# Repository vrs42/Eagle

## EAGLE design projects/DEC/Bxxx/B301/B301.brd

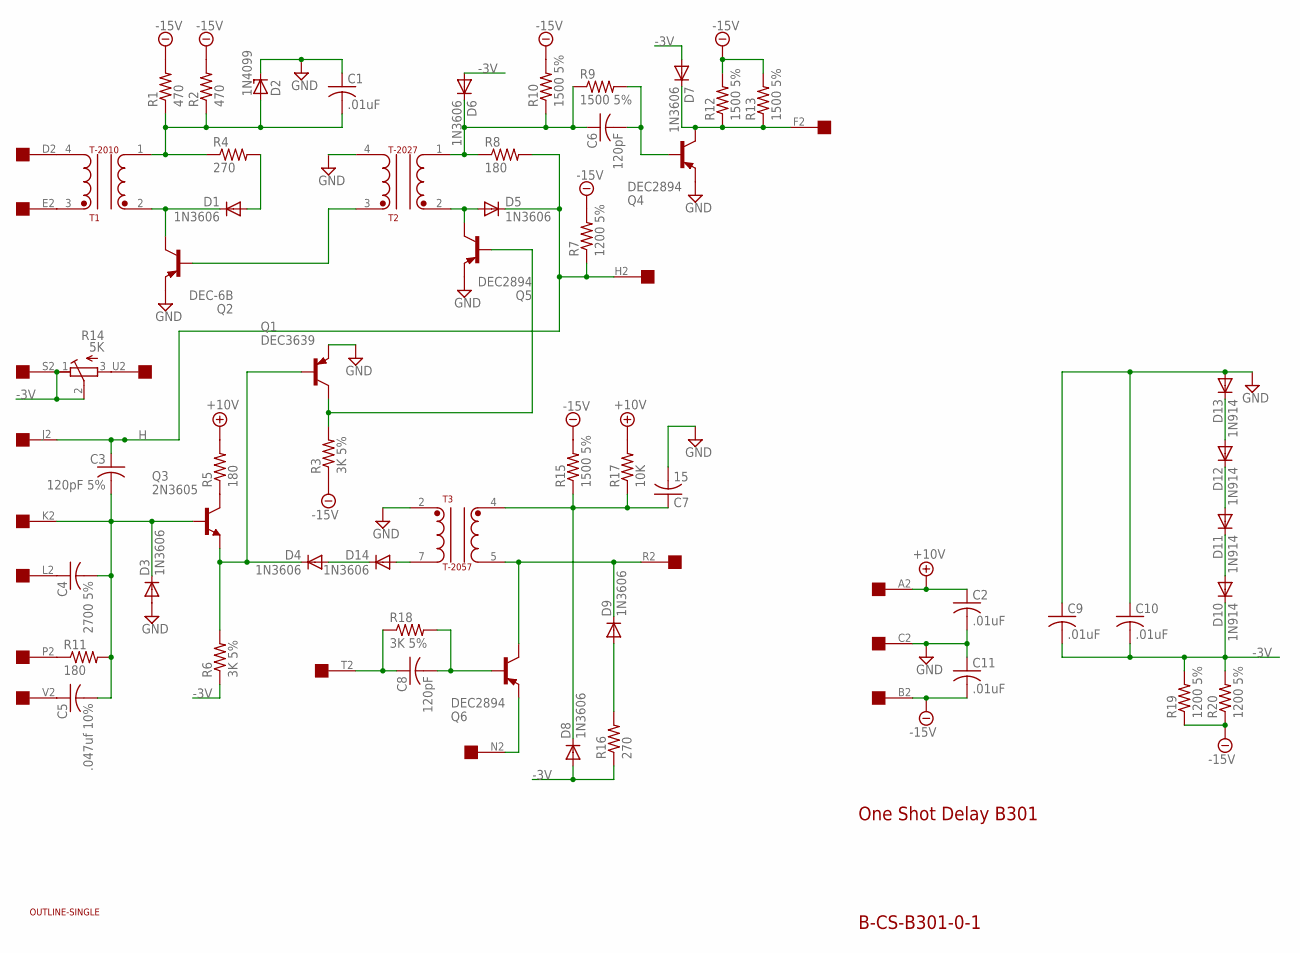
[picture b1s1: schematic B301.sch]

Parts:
C1, C2, C9, C10, C11: .01uF; C050-025X075
C3: 120pF 5%; C050-025X075
C4: 2700 5%; C102-043X133
C5: .047uf 10%; C225-062X268
C6, C8: 120pF; C050-025X075
C7: 15; C050-025X075
D1, D3, D4, D5, D6, D7, D8, D9, D14: 1N3606; DO35-10
D2: 1N4099; DO35Z10
D10, D11, D12, D13: 1N914; DO35-10
Q1: DEC3639; TO39
Q2: DEC-6B; TO39
Q3: 2N3605; TO39
Q4, Q5, Q6: DEC2894; TO39
R1, R2: 470; 0207/10
R3, R6, R18: 3K 5%; 0207/10
R4, R16: 270; 0207/10
R5, R8, R11: 180; 0207/10
R7, R19, R20: 1200 5%; 0207/10
R9, R10, R12, R13, R15: 1500 5%; 0207/10
R14: 5K; 3006Y
R17: 10K; 0207/10
T1: T-2010; TRANSFORMER2
T2: T-2027; TRANSFORMER2
T3: T-2057; TRANSFORMER
U$1: OUTLINE-SINGLE; SINGLE
U$2: EDGE-1; EDGE-CON1

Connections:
+10V: C2.1, R5.2, R17.2, U$2.A2
-3V: C9.2, C10.2, D6.A, D7.A, D8.A, D10.C, R6.1, R14.1 (A), R14.2 (S), R16.1, R19.2, R20.2, U$2.S2
-15V: C11.2, R1.2, R2.2, R3.1, R7.2, R10.2, R12.2, R13.2, R15.2, R19.1, R20.1, U$2.B2
GND: C1.1, C2.2, C7.2, C9.1, C10.1, C11.1, D2.C, D3.A, D13.A, Q1.1 (E), Q2.1 (E), Q4.1 (E), Q5.1 (E), T2.4, T3.2, U$2.C2
H: C3.1, D5.C, R7.1, R8.2, U$2.H2, U$2.J2
unnamed: D7.C, Q4.3 (C), R12.1, R13.1, U$2.F2
unnamed: C6.2, Q4.2 (B), R9.2
unnamed: D4.A, D14.C
unnamed: C3.2, C4.2, C5.2, D3.C, Q3.2 (B), R11.2, U$2.K2
unnamed: R14.3 (E), U$2.U2
unnamed: C4.1, U$2.L2
unnamed: C5.1, U$2.V2
unnamed: Q2.2 (B), T2.3
unnamed: D1.C, Q2.3 (C), T1.2
unnamed: R11.1, U$2.P2
unnamed: Q3.3 (C), R5.1
unnamed: C1.2, D2.A, R1.1, R2.1, R4.1, T1.1
unnamed: D1.A, R4.2
unnamed: D5.A, Q5.3 (C), T2.2
unnamed: D4.C, Q1.2 (B), Q3.1 (E), R6.2
unnamed: C6.1, D6.C, R8.1, R9.1, R10.1, T2.1
unnamed: Q1.3 (C), Q5.2 (B), R3.2
unnamed: D14.A, T3.7
unnamed: D9.C, Q6.3 (C), T3.5, U$2.R2
unnamed: Q6.1 (E), U$2.N2
unnamed: C8.2, Q6.2 (B), R18.2
unnamed: C8.1, R18.1, U$2.T2
unnamed: C7.1, D8.C, R15.1, R17.1, T3.4
unnamed: D9.A, R16.2
unnamed: D12.A, D13.C
unnamed: D11.A, D12.C
unnamed: D10.A, D11.C
unnamed: T1.3, U$2.E2
unnamed: T1.4, U$2.D2

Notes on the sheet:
One Shot Delay B301
B-CS-B301-0-1

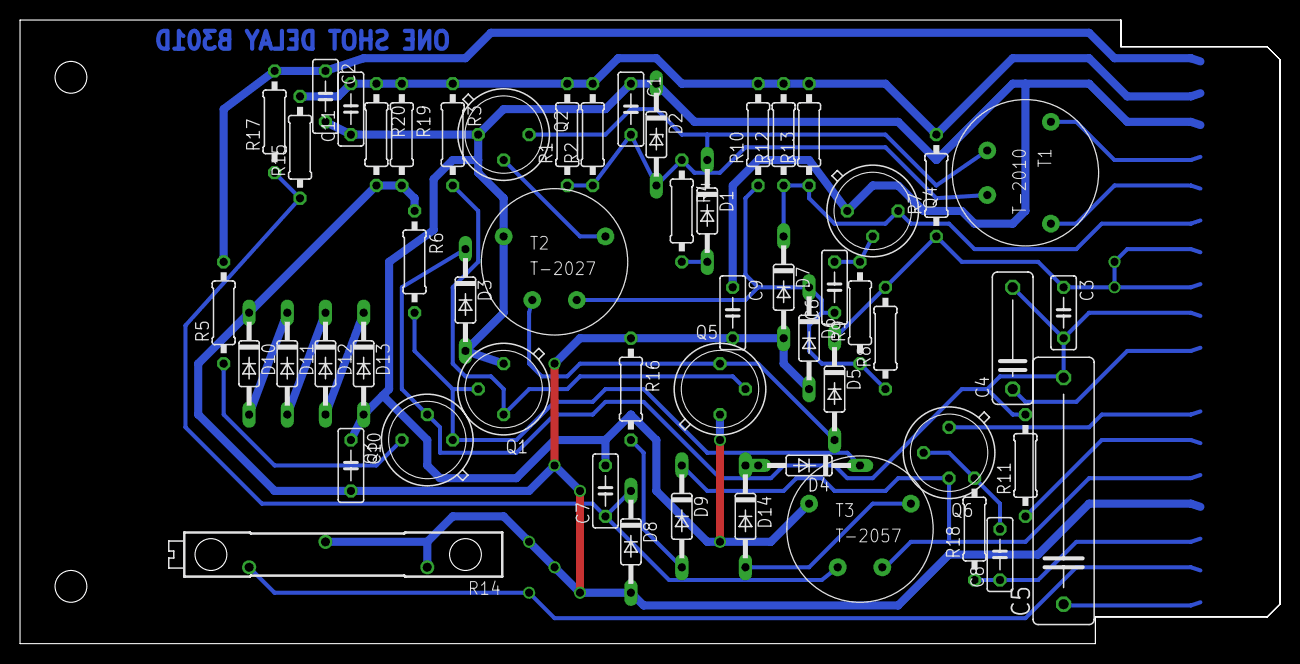
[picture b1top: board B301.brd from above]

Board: 2 copper layers, 125.7 x 62.2 mm, 56 parts (0 on the bottom side), 34 nets.

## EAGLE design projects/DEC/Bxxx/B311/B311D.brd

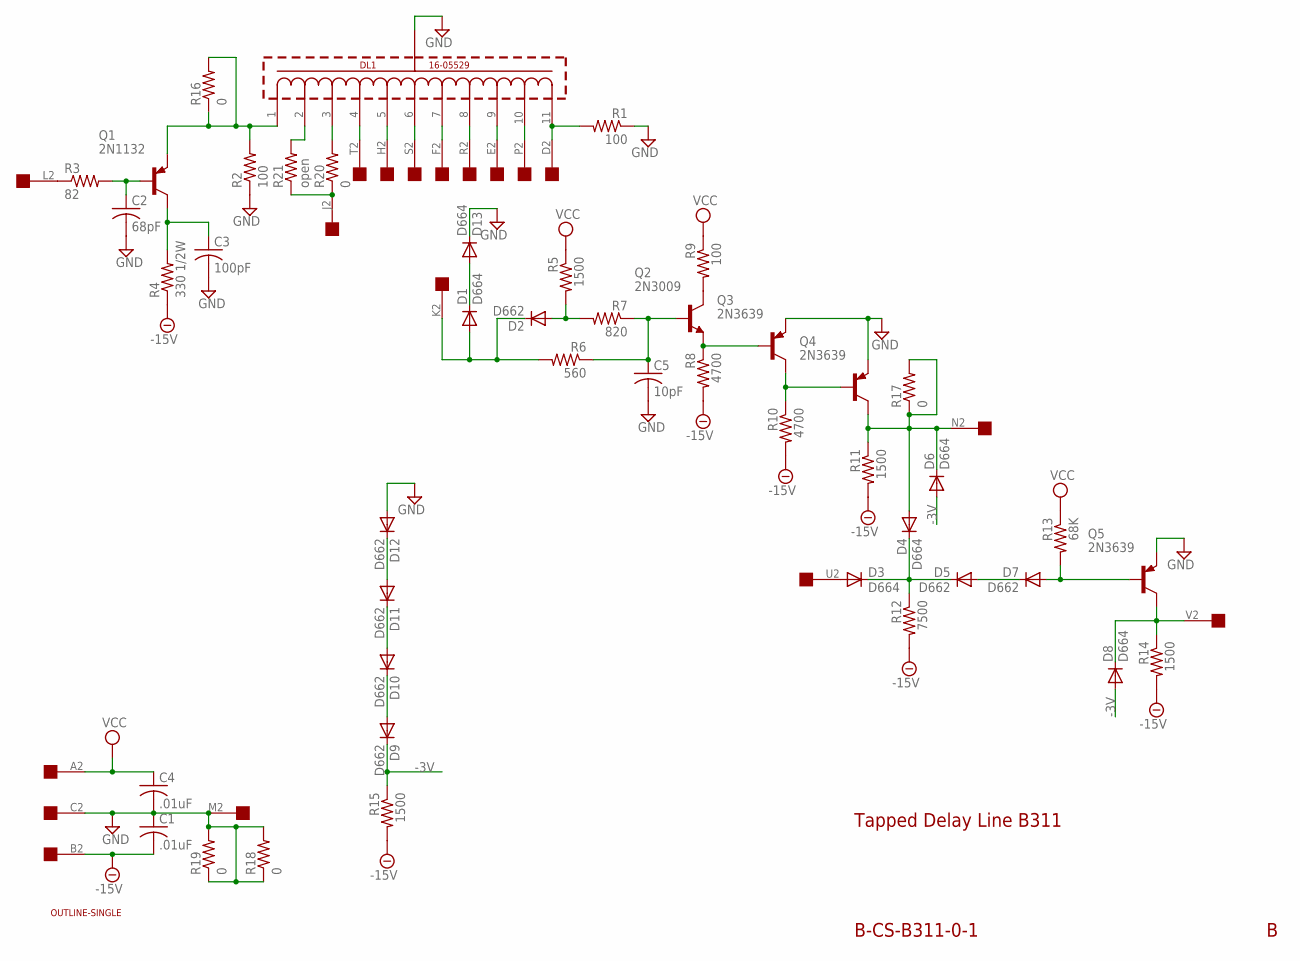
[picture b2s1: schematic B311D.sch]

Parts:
C1, C4: .01uF; C063-025X075
C2: 68pF; C063-025X075
C3: 100pF; C063-025X075
C5: 10pF; C063-025X075
D1, D3, D4, D6, D8, D13: D664; DO35-10
D2, D5, D7, D9, D10, D11, D12: D662; DO35-10
DL1: 16-05529
Q1: 2N1132; TO5
Q2: 2N3009; TO5
Q3, Q4, Q5: 2N3639; TO5
R1, R2, R9: 100; 0207/10
R3: 82; 0207/10
R4: 330 1/2W; 0411/15
R5, R11, R14, R15: 1500; 0207/10
R6: 560; 0207/10
R7: 820; 0207/10
R8, R10: 4700; 0207/10
R12: 7500; 0207/10
R13: 68K; 0207/10
R16, R17, R18, R19, R20: 0; 0207/10
R21: open; 0207/10
U$1: OUTLINE-SINGLE; SINGLE
U$2: EDGE-1; EDGE-CON1

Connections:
-3V: D6.A, D8.A, D9.C, R15.1
-15V: C1.2, R4.1, R8.2, R10.2, R11.2, R12.2, R14.2, R15.2, U$2.B2
GND: C1.1, C2.2, C3.2, C4.2, C5.2, D12.A, D13.C, DL1.12 (GND), Q3.1 (E), Q4.1 (E), Q5.1 (E), R1.1, R2.1, R18.1, R18.2, R19.1, R19.2, U$2.C2, U$2.M2
unnamed: DL1.11 (50), R1.2, U$2.D2
unnamed: DL1.10 (45), U$2.P2
unnamed: DL1.9 (40), U$2.E2
unnamed: DL1.8 (35), U$2.R2
unnamed: DL1.3 (10), R20.2
unnamed: DL1.4 (15), U$2.T2
unnamed: DL1.5 (20), U$2.H2
unnamed: DL1.6 (25), U$2.S2
unnamed: DL1.7 (30), U$2.F2
unnamed: R20.1, R21.1, U$2.J2
unnamed: DL1.2 (5), R21.2
unnamed: DL1.1 (0), Q1.1 (E), R2.2, R16.1, R16.2
unnamed: C2.1, Q1.2 (B), R3.2
unnamed: R3.1, U$2.L2
unnamed: C3.1, Q1.3 (C), R4.2
unnamed: D1.A, D2.C, R6.2, U$2.K2
unnamed: D1.C, D13.A
unnamed: D2.A, R5.2, R7.2
unnamed: C5.1, Q2.2 (B), R6.1, R7.1
unnamed: Q2.3 (C), R9.2
unnamed: Q2.1 (E), Q3.2 (B), R8.1
unnamed: Q3.3 (C), Q4.2 (B), R10.1
unnamed: D4.A, D6.C, Q4.3 (C), R11.1, R17.1, R17.2, U$2.N2
unnamed: D11.A, D12.C
unnamed: D9.A, D10.C
unnamed: D10.A, D11.C
unnamed: D3.A, U$2.U2
unnamed: D3.C, D4.C, D5.C, R12.1
unnamed: D5.A, D7.C
unnamed: D7.A, Q5.2 (B), R13.2
unnamed: D8.C, Q5.3 (C), R14.1, U$2.V2
VCC: C4.1, R5.1, R9.1, R13.1, U$2.A2

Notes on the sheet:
Tapped Delay Line B311
B-CS-B311-0-1

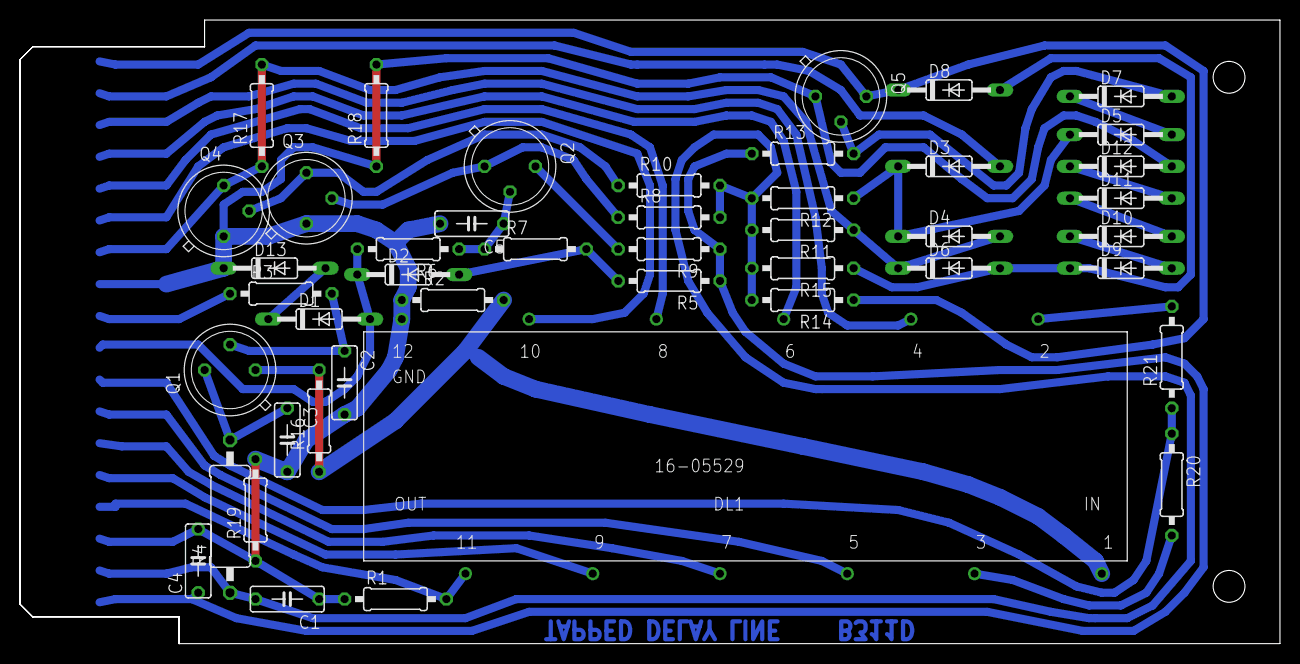
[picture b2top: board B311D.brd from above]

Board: 2 copper layers, 125.7 x 62.2 mm, 47 parts (0 on the bottom side), 35 nets.

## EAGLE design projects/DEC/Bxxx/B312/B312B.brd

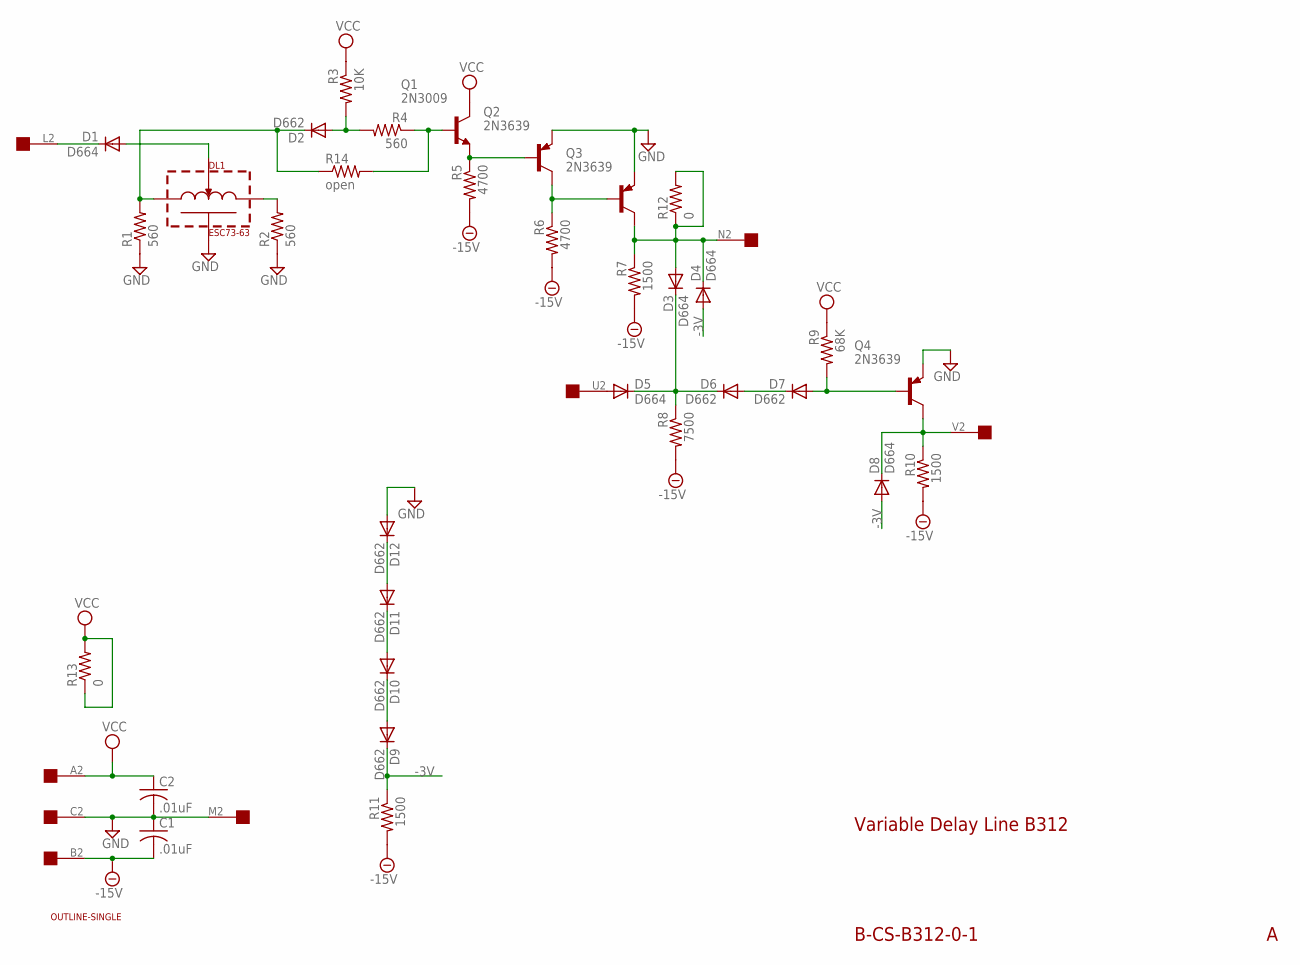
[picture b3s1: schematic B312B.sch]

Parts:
C1, C2: .01uF; C063-025X075
D1, D3, D4, D5, D8: D664; DO35-10
D2, D6, D7, D9, D10, D11, D12: D662; DO35-10
DL1: ESC73-63; DELAYLINE
Q1: 2N3009; TO5
Q2, Q3, Q4: 2N3639; TO5
R1, R2, R4: 560; 0207/10
R3: 10K; 0207/10
R5, R6: 4700; 0207/10
R7, R10, R11: 1500; 0207/10
R8: 7500; 0207/10
R9: 68K; 0207/10
R12, R13: 0; 0207/10
R14: open; 0207/10
U$1: OUTLINE-SINGLE; SINGLE
U$2: EDGE-1; EDGE-CON1

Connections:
-3V: D4.A, D8.A, D9.C, R11.1
-15V: C1.2, R5.2, R6.2, R7.2, R8.2, R10.2, R11.2, U$2.B2
GND: C1.1, C2.2, D12.A, DL1.G, Q2.1 (E), Q3.1 (E), Q4.1 (E), R1.1, R2.1, U$2.C2, U$2.M2
unnamed: D2.C, DL1.L, R1.2, R14.1
unnamed: DL1.R, R2.2
unnamed: D1.A, DL1.V
unnamed: D1.C, U$2.L2
unnamed: D2.A, R3.2, R4.2
unnamed: Q1.2 (B), R4.1, R14.2
unnamed: Q1.1 (E), Q2.2 (B), R5.1
unnamed: Q2.3 (C), Q3.2 (B), R6.1
unnamed: D3.A, D4.C, Q3.3 (C), R7.1, R12.1, R12.2, U$2.N2
unnamed: D11.A, D12.C
unnamed: D9.A, D10.C
unnamed: D10.A, D11.C
unnamed: D5.A, U$2.U2
unnamed: D3.C, D5.C, D6.C, R8.1
unnamed: D6.A, D7.C
unnamed: D7.A, Q4.2 (B), R9.2
unnamed: D8.C, Q4.3 (C), R10.1, U$2.V2
VCC: C2.1, Q1.3 (C), R3.1, R9.1, R13.1, R13.2, U$2.A2

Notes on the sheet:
Variable Delay Line B312
B-CS-B312-0-1

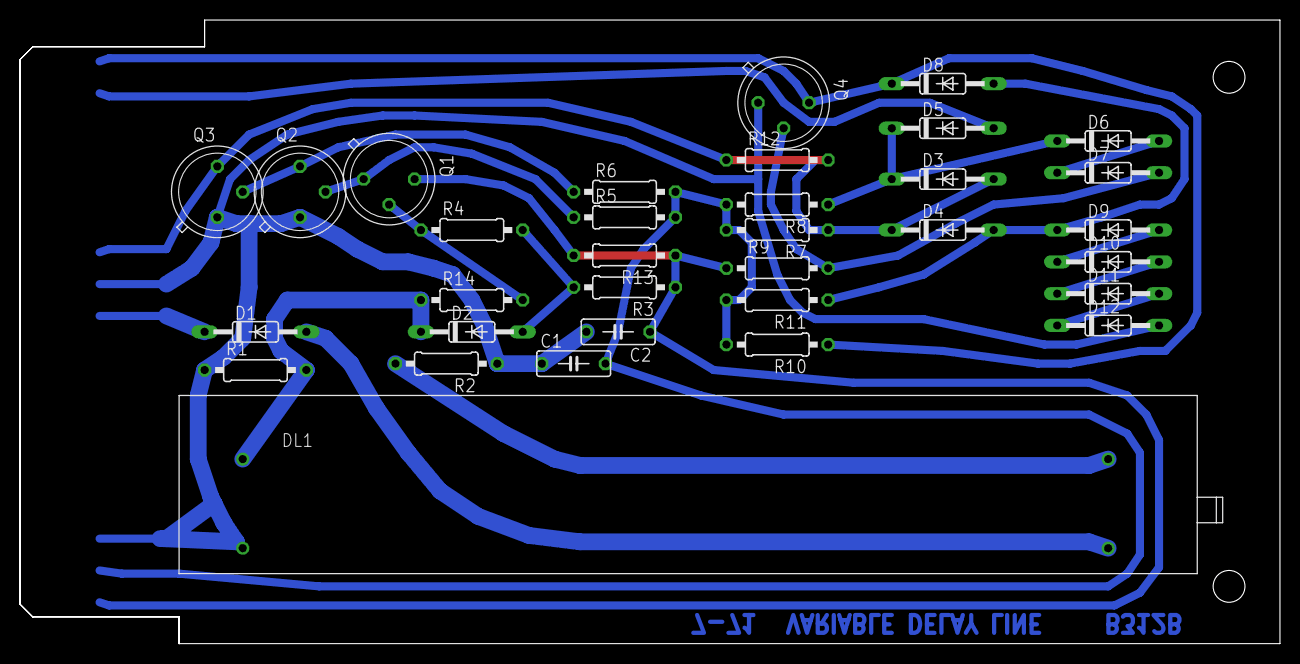
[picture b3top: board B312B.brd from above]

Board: 2 copper layers, 125.7 x 62.2 mm, 35 parts (0 on the bottom side), 21 nets.

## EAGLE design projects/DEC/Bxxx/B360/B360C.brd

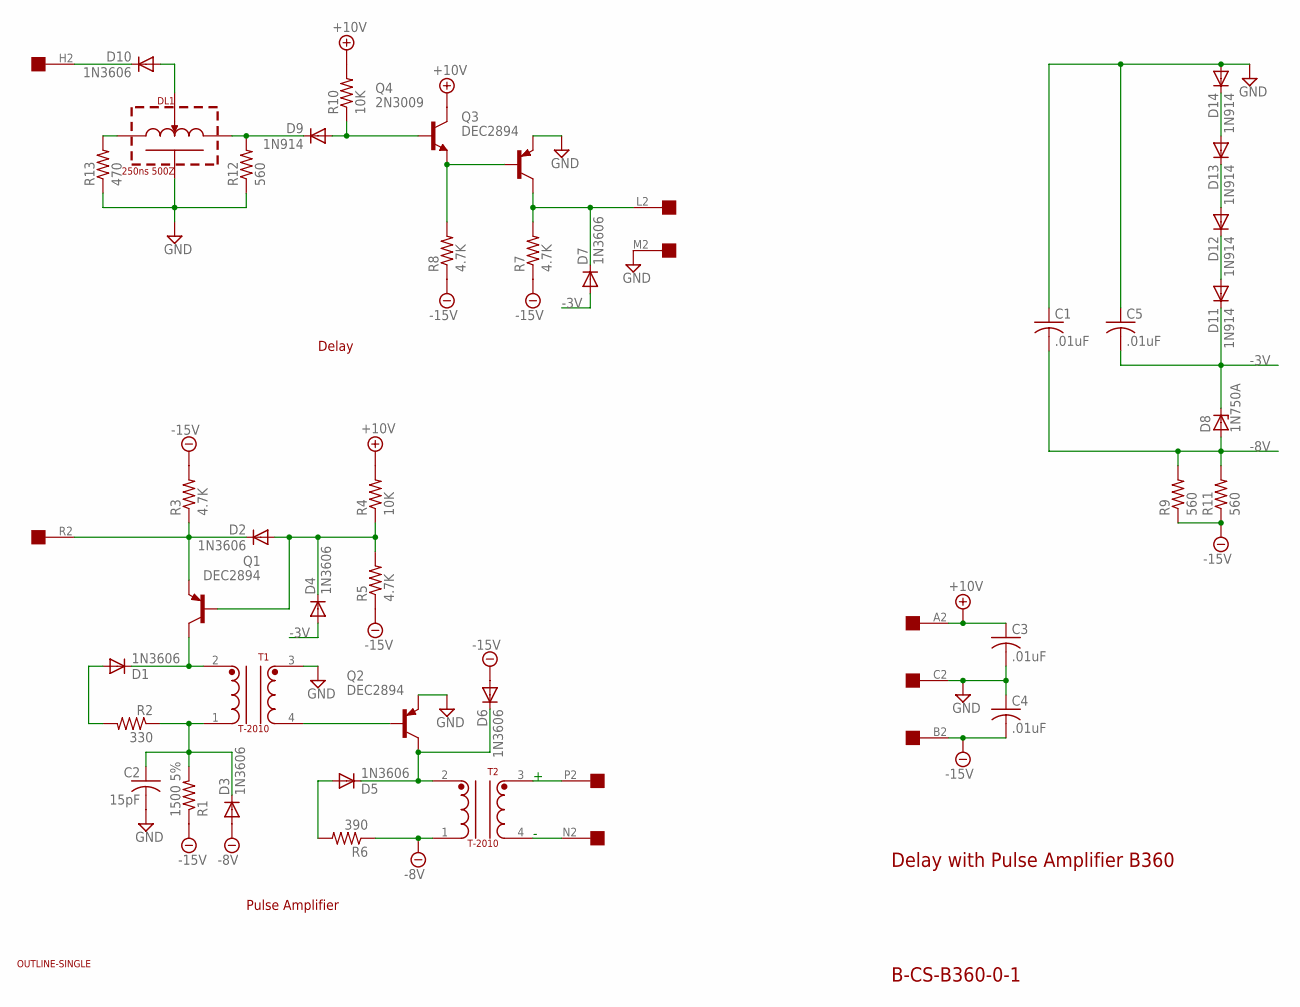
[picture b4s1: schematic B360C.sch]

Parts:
C1, C3, C4, C5: .01uF; C050-025X075
C2: 15pF; C050-025X075
D1, D2, D3, D4, D5, D6, D7, D10: 1N3606; DO35-10
D8: 1N750A; DO35Z10
D9, D11, D12, D13, D14: 1N914; DO35-10
DL1: 250ns 500Z; DELAYLINE
Q1, Q2, Q3: DEC2894; TO39
Q4: 2N3009; TO39
R1: 1500 5%; 0207/10
R2: 330; 0207/10
R3, R5, R7, R8: 4.7K; 0207/10
R4, R10: 10K; 0207/10
R6: 390; 0207/10
R9, R11, R12: 560; 0207/10
R13: 470; 0207/10
T1, T2: T-2010; TRANSFORMER2
U$1: OUTLINE-SINGLE; SINGLE
U$2: EDGE-1; EDGE-CON1

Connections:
+10V: C3.1, Q4.3 (C), R4.2, R10.2, U$2.A2
-3V: C5.2, D4.A, D7.A, D8.C, D11.C
-8V: C1.2, D3.A, D8.A, R6.1, R9.2, R11.2, T2.1
-15V: C4.2, D6.A, R1.1, R3.2, R5.1, R7.1, R8.1, R9.1, R11.1, U$2.B2
GND: C1.1, C2.2, C3.2, C4.1, C5.1, D14.A, DL1.G, Q2.1 (E), Q3.1 (E), R12.1, R13.1, T1.3, U$2.C2, U$2.M2
unnamed: DL1.R, R13.2
unnamed: D10.A, DL1.V
unnamed: T2.3, U$2.P2
unnamed: T2.4, U$2.N2
unnamed: D10.C, U$2.H2
unnamed: D5.C, D6.C, Q2.3 (C), T2.2
unnamed: D9.C, DL1.L, R12.2
unnamed: Q2.2 (B), T1.4
unnamed: D1.C, Q1.3 (C), T1.2
unnamed: D5.A, R6.2
unnamed: Q3.2 (B), Q4.1 (E), R8.2
unnamed: D1.A, R2.2
unnamed: C2.1, D3.C, R1.2, R2.1, T1.1
unnamed: D9.A, Q4.2 (B), R10.1
unnamed: D2.C, Q1.1 (E), R3.1, U$2.R2
unnamed: D7.C, Q3.3 (C), R7.2, U$2.L2
unnamed: D2.A, D4.C, Q1.2 (B), R4.1, R5.2
unnamed: D13.A, D14.C
unnamed: D12.A, D13.C
unnamed: D11.A, D12.C

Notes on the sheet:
Delay with Pulse Amplifier B360
B-CS-B360-0-1
Pulse Amplifier
Delay

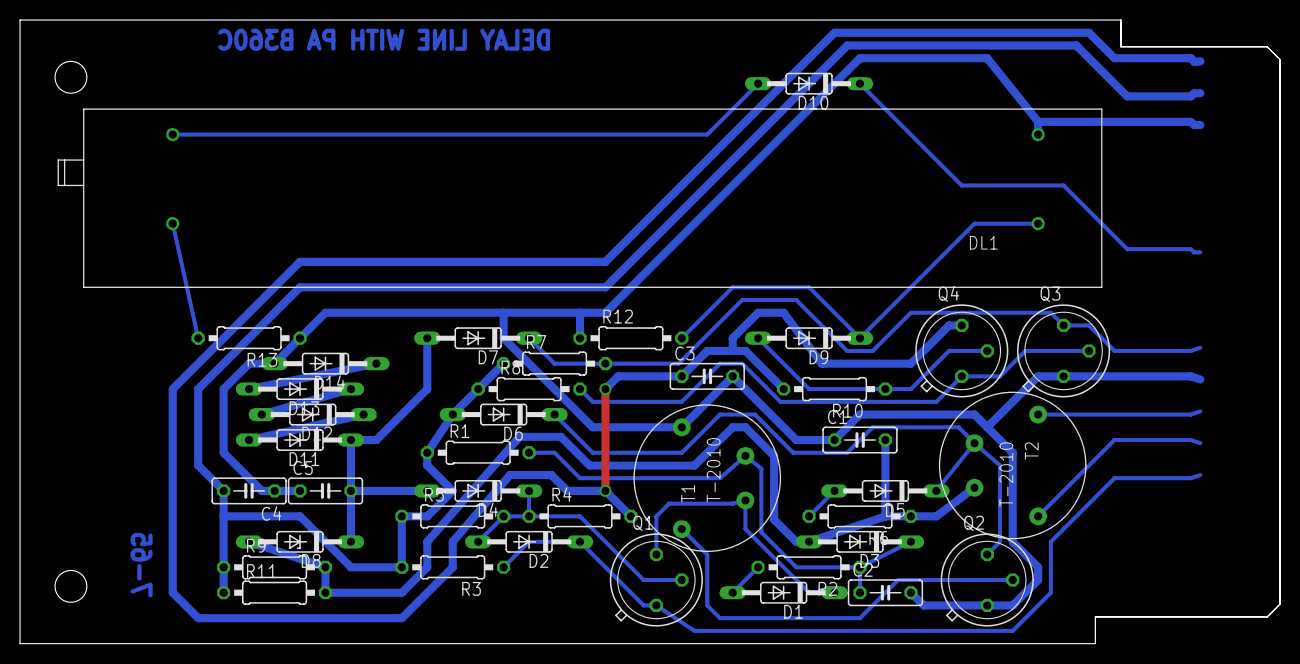
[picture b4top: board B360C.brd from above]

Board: 2 copper layers, 125.7 x 62.2 mm, 41 parts (0 on the bottom side), 25 nets.

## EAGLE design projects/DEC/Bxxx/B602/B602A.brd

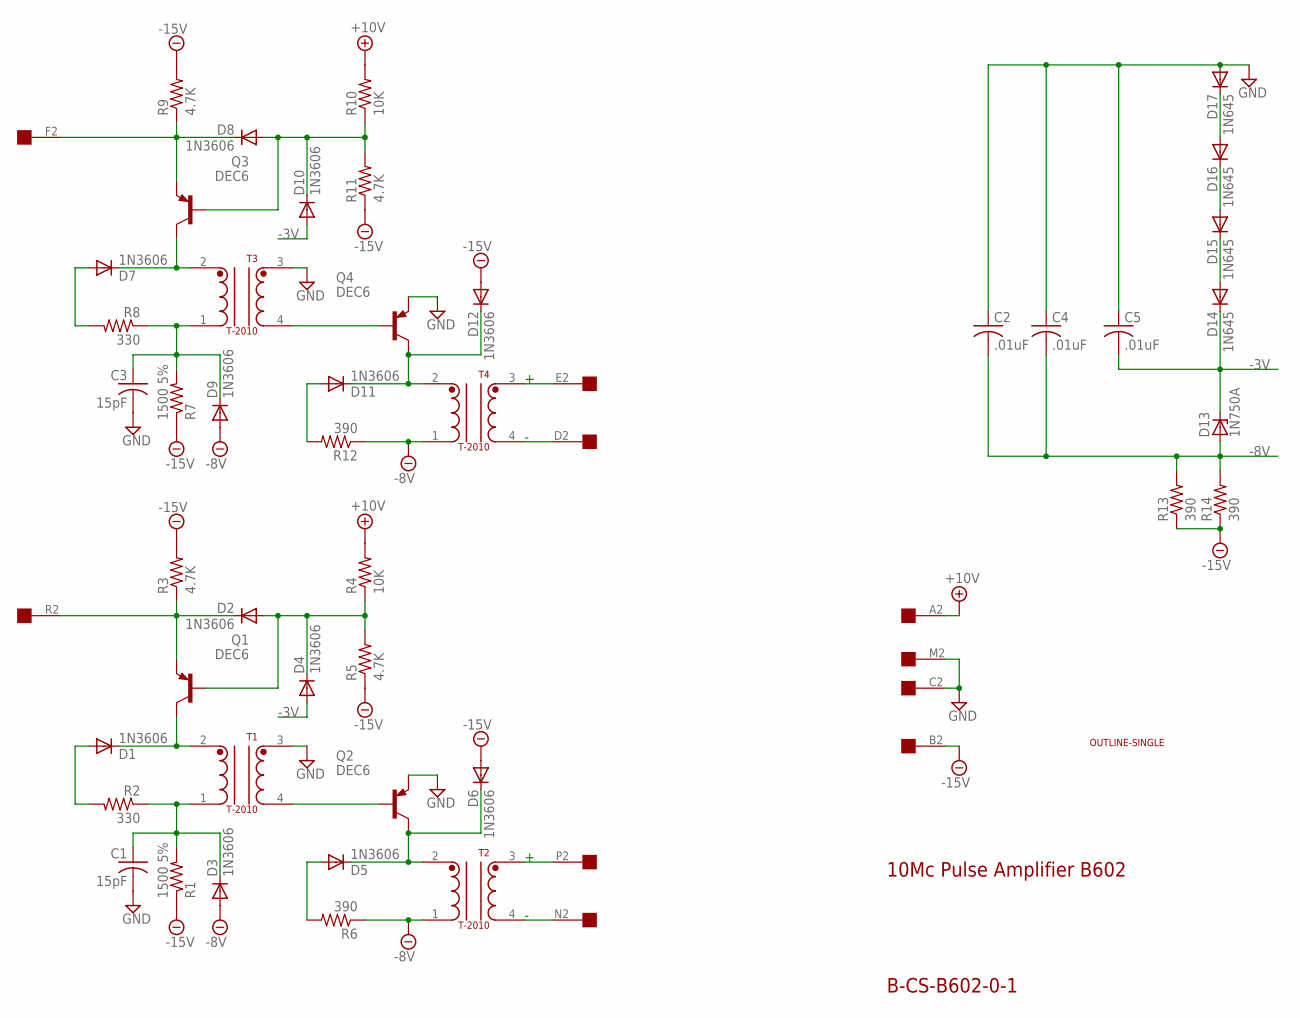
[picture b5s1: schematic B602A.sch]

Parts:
C1, C3: 15pF; C050-025X075
C2, C4, C5: .01uF; C050-025X075
D1, D2, D3, D4, D5, D6, D7, D8, D9, D10, D11, D12: 1N3606; DO35-10
D13: 1N750A; DO35Z10
D14, D15, D16, D17: 1N645; DO35-10
Q1, Q2, Q3, Q4: DEC6; TO39
R1, R7: 1500 5%; 0207/10
R2, R8: 330; 0207/10
R3, R5, R9, R11: 4.7K; 0207/10
R4, R10: 10K; 0207/10
R6, R12, R13, R14: 390; 0207/10
T1, T2, T3, T4: T-2010; TRANSFORMER2
U$1: OUTLINE-SINGLE; SINGLE
U$2: EDGE-1; EDGE-CON1

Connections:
+10V: R4.2, R10.2, U$2.A2
-3V: C5.2, D4.A, D10.A, D13.C, D14.C
-8V: C2.2, C4.2, D3.A, D9.A, D13.A, R6.1, R12.1, R13.2, R14.2, T2.1, T4.1
-15V: D6.A, D12.A, R1.1, R3.2, R5.1, R7.1, R9.2, R11.1, R13.1, R14.1, U$2.B2
GND: C1.2, C2.1, C3.2, C4.1, C5.1, D17.A, Q2.1 (E), Q4.1 (E), T1.3, T3.3, U$2.C2, U$2.M2
unnamed: D7.C, Q3.3 (C), T3.2
unnamed: D7.A, R8.2
unnamed: T2.3, U$2.P2
unnamed: T2.4, U$2.N2
unnamed: T4.3, U$2.E2
unnamed: D5.C, D6.C, Q2.3 (C), T2.2
unnamed: T4.4, U$2.D2
unnamed: Q2.2 (B), T1.4
unnamed: D1.C, Q1.3 (C), T1.2
unnamed: D5.A, R6.2
unnamed: D11.C, D12.C, Q4.3 (C), T4.2
unnamed: D11.A, R12.2
unnamed: D1.A, R2.2
unnamed: C1.1, D3.C, R1.2, R2.1, T1.1
unnamed: Q4.2 (B), T3.4
unnamed: C3.1, D9.C, R7.2, R8.1, T3.1
unnamed: D2.C, Q1.1 (E), R3.1, U$2.R2
unnamed: D8.C, Q3.1 (E), R9.1, U$2.F2
unnamed: D2.A, D4.C, Q1.2 (B), R4.1, R5.2
unnamed: D8.A, D10.C, Q3.2 (B), R10.1, R11.2
unnamed: D16.A, D17.C
unnamed: D15.A, D16.C
unnamed: D14.A, D15.C

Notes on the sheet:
10Mc Pulse Amplifier B602
B-CS-B602-0-1

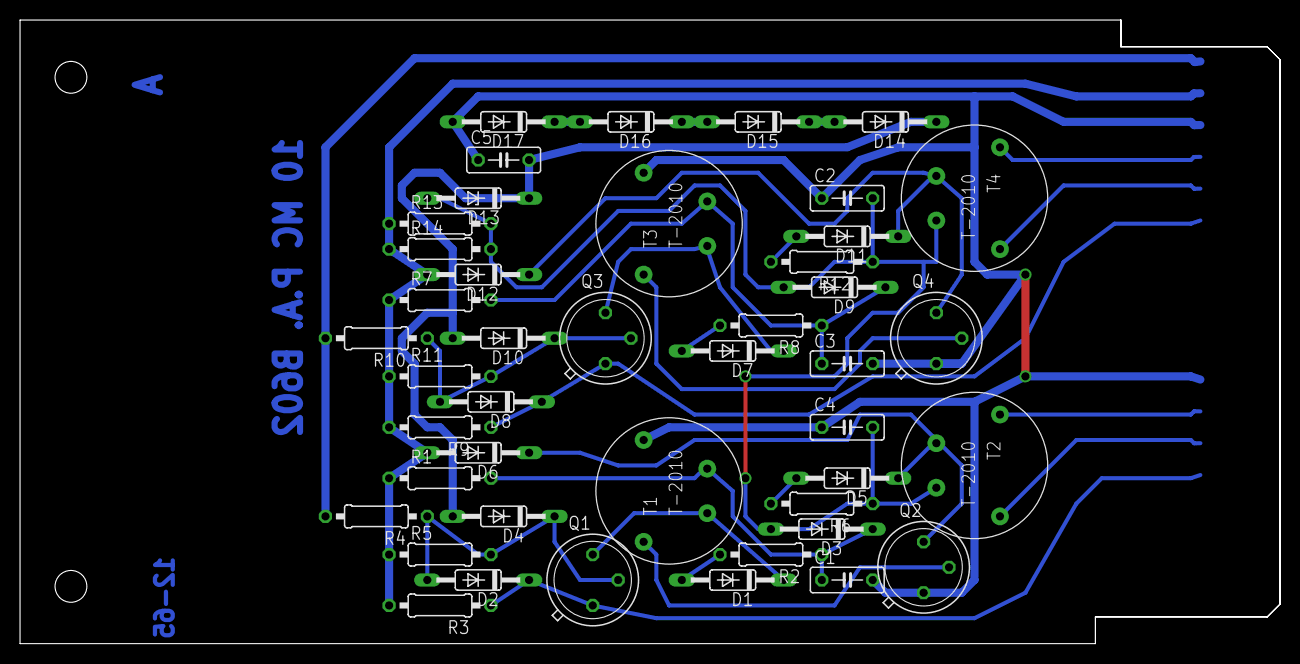
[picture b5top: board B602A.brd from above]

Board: 2 copper layers, 125.7 x 62.2 mm, 46 parts (0 on the bottom side), 28 nets.
